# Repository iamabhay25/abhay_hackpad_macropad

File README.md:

# Abhay's Hackpad Macropad
My personal macropad for everyday use. 

Bill of Materials: <br>
- 6x Cherry MX Switches<br>
- 2x SK6812 MINI Leds<br>
- 1x XIAO RP2040<br>
- 6x Blank DSA Keycaps<br>
- 4x M3x16 Bolt<br>
- 4x M3 Heatset<br>

Schematic:

PCB:

Macroboard Bottom Case CAD:

W/PCB:

Macroboard Top Case CAD:

Macroboard Final Build:

W/ PCB:

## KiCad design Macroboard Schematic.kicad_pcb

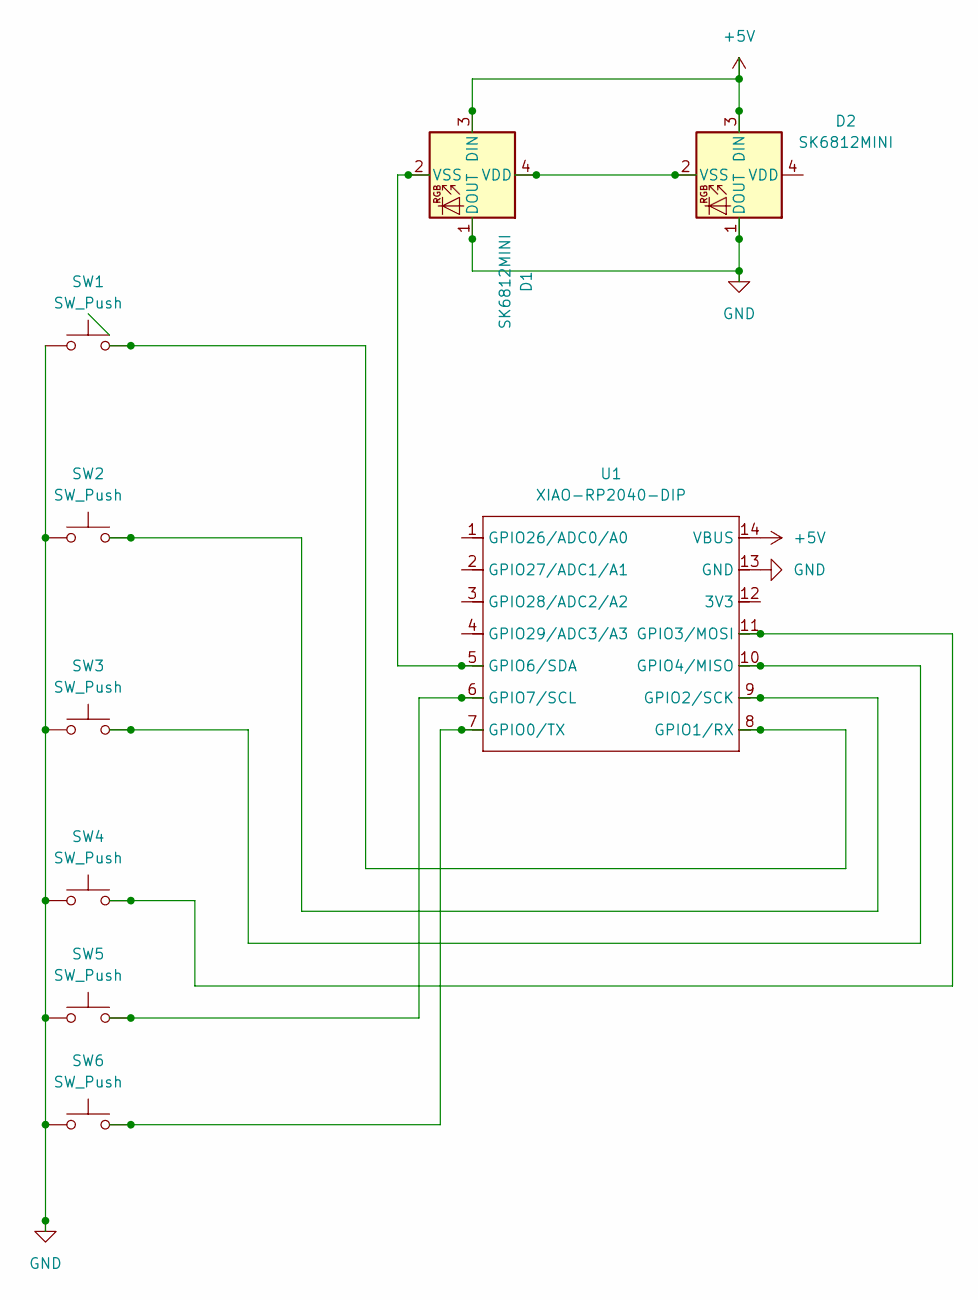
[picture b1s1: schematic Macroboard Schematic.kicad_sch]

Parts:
D1, D2: SK6812MINI; LED_SK6812MINI_PLCC4_3.5x3.5mm_P1.75mm
SW1, SW2, SW3, SW4, SW5, SW6: SW_Push; SW_Cherry_MX_1.00u_PCB
U1: XIAO-RP2040-DIP

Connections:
+5V: D1.3 (DIN), D2.3 (DIN), U1.14 (VBUS)
GND: D1.1 (DOUT), D2.1 (DOUT), SW1.1, SW2.1, SW3.1, SW4.1, SW5.1, SW6.1, U1.13 (GND)
unnamed: D1.4 (VDD), D2.2 (VSS)
unnamed: D1.2 (VSS), U1.5 (GPIO6/SDA)
unnamed: SW6.2, U1.7 (GPIO0/TX)
unnamed: SW1.2, U1.8 (GPIO1/RX)
unnamed: SW2.2, U1.9 (GPIO2/SCK)
unnamed: SW4.2, U1.11 (GPIO3/MOSI)
unnamed: SW3.2, U1.10 (GPIO4/MISO)
unnamed: SW5.2, U1.6 (GPIO7/SCL)

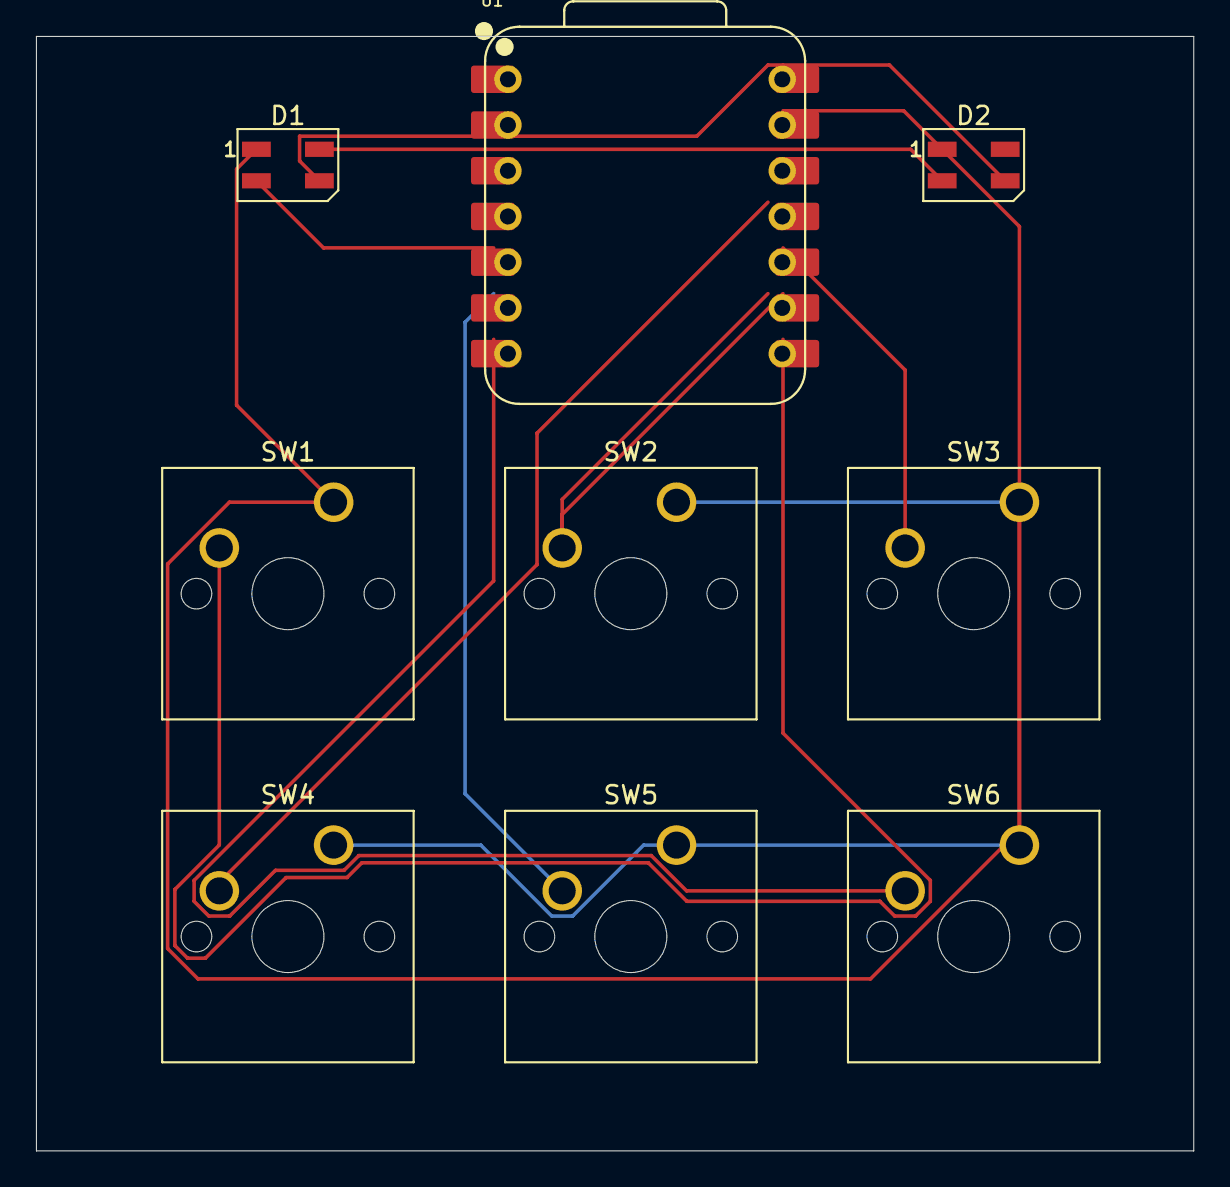
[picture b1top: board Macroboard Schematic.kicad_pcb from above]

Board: 2 copper layers, 64.3 x 61.9 mm, 9 parts (0 on the bottom side), 10 nets.

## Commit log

2026-01-28 Revise README title and description
    Updated project title and improved description formatting.
2026-01-28 Improve specifications formatting in README
    Updated specifications formatting in README.md
2026-01-28 Update README formatting for specifications section
2026-01-28 Remove duplicate specifications in README
    Updated specifications section to remove duplicates.
2026-01-28 Update schematic and PCB image references in README
2026-01-29 Update images in README for schematic and PCB
2026-01-29 Replace schematic and PCB images with higher resolution
    Updated schematic and PCB images with higher resolution versions.
2026-01-29 Create CAD
2026-01-29 Rename Abhay's+Macropad+Bottom.f3d to CAD/Abhay's+Macropad+Bottom.f3d
2026-01-29 Rename Abhay+Macroboard+Top.f3d to CAD/Abhay+Macroboard+Top.f3d
2026-01-29 Rename Macroboard Schematic.kicad_pcb to PCB/Macroboard Schematic.kicad_pcb
2026-01-29 Rename Macroboard Schematic.kicad_pro to PCB/Macroboard Schematic.kicad_pro
2026-01-29 Rename Macroboard Schematic.kicad_sch to PCB/Macroboard Schematic.kicad_sch
2026-01-29 Rename abhay_macroboard_firmware.py to FIRMWARE/abhay_macroboard_firmware.py
